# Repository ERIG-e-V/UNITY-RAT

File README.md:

# UNITY-RAT
RAT - Recovery Actuation and Tracking Board; Deploys and monitors the main and secondary parachute of the two staged UNITY recovery system

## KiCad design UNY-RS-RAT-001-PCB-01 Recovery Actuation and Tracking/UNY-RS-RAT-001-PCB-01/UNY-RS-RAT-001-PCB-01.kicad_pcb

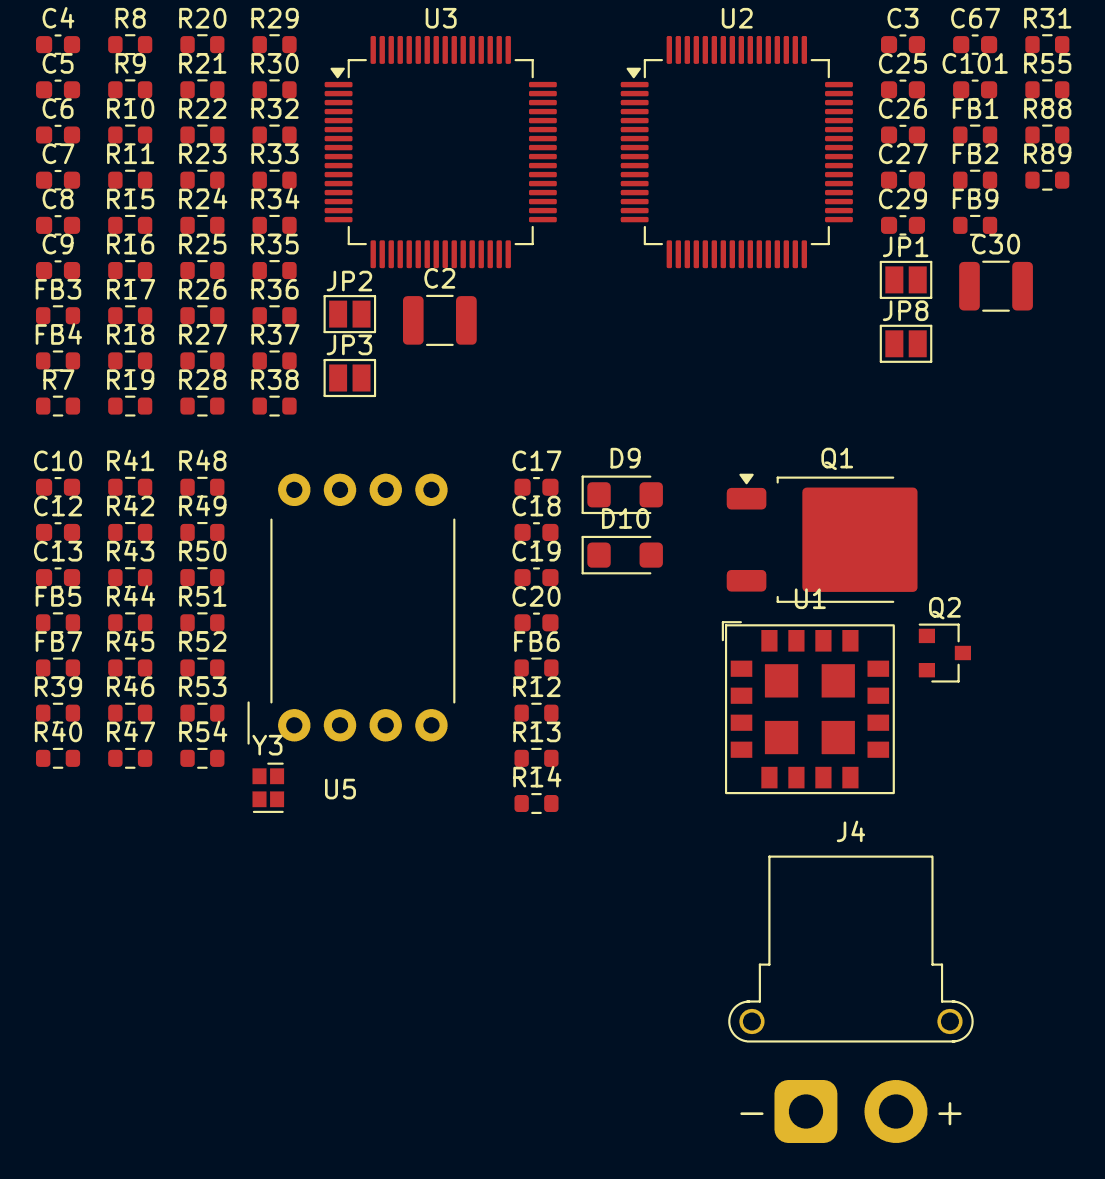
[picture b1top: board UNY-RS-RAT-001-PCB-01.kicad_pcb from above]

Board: 2 copper layers, 95 parts (0 on the bottom side), 45 nets, no tracks yet.

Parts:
C2, C30: 4.7uF; C_1210_3225Metric
C3, C4, C5, C6, C7, C8, C9, C12, C13, C18, C25, C26, C27, C29, C67, C101: 100nF; C_0603_1608Metric
C10: 100n; C_0603_1608Metric
C17, C20: 220pF; C_0603_1608Metric
C19: 100pF; C_0603_1608Metric
D9, D10: SMF5V0A; D_SMF
FB1, FB2, FB3, FB4, FB5, FB6, FB7, FB9: 470R; R_0603_1608Metric
J4: XT30PW-F; AMASS_XT30PW-F_1x02_P2.50mm_Horizontal
JP1, JP2, JP3, JP8: Solderbridge; SolderJumper-2_P1.3mm_Open_Pad1.0x1.5mm
Q1: STD95P3LLH6AG; TO-252-2
Q2: NTR4003NT1G; SOT-23
R7, R8, R9, R10, R11, R13, R15, R16, R17, R18, R19, R20, R21, R22, R23, R24, R25, R26, R27, R28, R29, R30, R31, R32, R33, R34, R35, R36, R37, R38, R39, R40, R41, R42, R43, R44, R55, R88, R89: 10kR; R_0603_1608Metric
R12, R14: 60R; R_0603_1608Metric
R45, R46, R47, R48, R49, R50, R51, R52, R53, R54: 0; R_0603_1608Metric
U1: LGA-16EP_171011801; U_Wurth_WPME-VDLM-LGA-16EP
U2, U3: STM32G474RETx; LQFP-64_10x10mm_P0.5mm
U5: HSCDANN150PASA5
Y3: IQXO-540_831056239; Y_Wurth_WE-SPXO-IQXO-540

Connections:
+3V3: FB1.1, FB2.1, FB3.1, FB4.1, FB5.2, FB6.1, FB7.2, FB9.1, JP1.2 (B), JP2.2 (B), JP3.2 (B), JP8.2 (B), R8.1, R11.1, R17.1, R20.1, R23.1, R26.1, R29.1, R33.1, R36.1, R88.1, R89.1, U1.9 (VOUT), U1.10 (VOUT), U1.11 (VOUT), U1.12 (VOUT)
+12V: Q1.2 (D), U1.1 (VIN), U1.2 (VIN), U1.3 (VIN), U1.4 (VIN)
/CAN/CAN_EXT_N: C17.2, D9.1 (A1), R12.1
/CAN/CAN_EXT_P: C20.1, D10.1 (A1), R14.2
/Controller Unit/Deployment Controller/ARM_SAFE: R37.1, U3.4 (PC15)
/Controller Unit/Deployment Controller/ARM_check: R36.2, R37.2, R38.1
/Controller Unit/Deployment Controller/MP0_IN: R8.2, R9.2, R10.1
/Controller Unit/Deployment Controller/MP0_SAFE: R9.1, U3.39 (PC7)
/Controller Unit/Deployment Controller/MP1_IN: R11.2, R15.2, R16.1
/Controller Unit/Deployment Controller/MP1_SAFE: R15.1, U3.40 (PC8)
/Controller Unit/Deployment Controller/MP2_IN: R17.2, R18.2, R19.1
/Controller Unit/Deployment Controller/MP2_SAFE: R18.1, U3.41 (PC9)
/Controller Unit/Deployment Controller/MP3_IN: R20.2, R21.2, R22.1
/Controller Unit/Deployment Controller/MP3_SAFE: R21.1, U3.52 (PC10)
/Controller Unit/Deployment Controller/MP4_IN: R23.2, R24.2, R25.1
/Controller Unit/Deployment Controller/MP4_SAFE: R24.1, U3.53 (PC11)
/Controller Unit/Deployment Controller/MP5_IN: R26.2, R27.2, R28.1
/Controller Unit/Deployment Controller/MP5_SAFE: R27.1, U3.54 (PC12)
/Controller Unit/Deployment Controller/MP6_IN: R29.2, R30.2, R32.1
/Controller Unit/Deployment Controller/MP6_SAFE: R30.1, U3.2 (PC13)
/Controller Unit/Deployment Controller/MP7_IN: R33.2, R34.2, R35.1
/Controller Unit/Deployment Controller/MP7_SAFE: R34.1, U3.3 (PC14)
/Controller Unit/Deployment Controller/Received_Feedback: R55.2, U3.8 (PC0)
/Sensor Input/3v3_Fsense: C12.1, C13.1, FB7.1, R39.1, R40.1, R43.1, Y3.1 (E/D), Y3.4 (+VS)
/Sensor Input/F_IN_0: R45.1, R47.1, R53.1
/Sensor Input/F_IN_1: R46.2, R48.2, R54.2
/Sensor Input/F_sense_CH0: R49.2, R51.2, R53.2
/Sensor Input/F_sense_CH1: R50.1, R52.1, R54.1
GND: C2.2, C3.2, C4.2, C5.2, C6.2, C7.2, C8.2, C9.2, C10.2, C12.2, C13.2, C17.1, C18.2, C19.2, C20.2, C25.2, C26.2, C27.2, C29.2, C30.2, C67.2, C101.2, D9.2 (A2), D10.2 (A2), Q2.2 (S), R7.1, R10.2, R13.2, R16.2, R19.2, R22.2, R25.2, R28.2, R31.1, R32.2, R35.2, R38.2, R41.2, R42.2, R44.2, U1.EP (PGND), U2.15 (VSS), U2.27 (VSSA), U2.31 (VSS), U2.47 (VSS), U2.63 (VSS), U3.15 (VSS), U3.27 (VSSA), U3.31 (VSS), U3.47 (VSS), U3.63 (VSS), U5.1, Y3.2 (GND)
unnamed: C19.1, R12.2, R14.1
unnamed: JP1.1 (A), JP8.1 (A), R31.2, U2.61 (PB8)
unnamed: JP2.1 (A), JP3.1 (A), R7.2, U3.61 (PB8)
unnamed: Q1.1 (G), Q2.3 (D)
unnamed: R40.2, R42.1, R52.2
unnamed: R41.1, R45.2, R46.1, R51.1
unnamed: R43.2, R44.1, R50.2
unnamed: R47.2, R48.1, R49.1
unnamed: R55.1, U2.4 (PC15)
unnamed: C25.1, C26.1, C27.1, C29.1, C30.1, C101.1, FB2.2, U2.1 (VBAT), U2.16 (VDD), U2.29 (VDDA), U2.32 (VDD), U2.48 (VDD), U2.64 (VDD)
unnamed: C2.1, C4.1, C5.1, C6.1, C7.1, C8.1, FB3.2, U3.1 (VBAT), U3.16 (VDD), U3.29 (VDDA), U3.32 (VDD), U3.48 (VDD), U3.64 (VDD)
unnamed: C18.1, FB6.2
unnamed: C10.1, FB5.1, U5.2 (Vcc)
unnamed: C67.1, FB9.2
unnamed: C3.1, FB1.2
unnamed: C9.1, FB4.2

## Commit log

2025-08-23 Project Setup
2025-09-12 First draft for ERBUS, Power & CPU
2025-09-14 Semi complete, missing footprints and connectors
